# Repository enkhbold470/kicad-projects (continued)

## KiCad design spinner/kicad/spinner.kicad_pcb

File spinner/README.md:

# Spinner

A 12-24 V field-oriented-control BLDC motor controller: STM32G431, three IR2104 half bridges, MT6701 encoder, CAN FD.

| Layers | Size | Parts | Nets | Connections routed | Vias | ERC errors | DRC errors / unconnected / parity |
|---|---|---|---|---|---|---|---|
| 4 | 84 x 66 mm | 87 | 52 | 205 -> 0 open | 167 | 0 | 0 / 0 / 0 |

**Not fabricated, assembled or powered.** Every number on this page is measured by KiCad 10 on the files in this folder; the full measurements are in [`report.json`](report.json).

| | |
|---|---|
| KiCad project | [`kicad/`](kicad/) |
| Gerbers, BOM, CPL, STEP, schematic PDF | [`fab/`](fab/) |
| Renders | [top](media/top.png), [bottom](media/bottom.png) |
| Design process, every step as KiCad rendered it | [`media/design-process.mp4`](media/design-process.mp4) |

Spinner is a field-oriented-control (FOC) controller for a three-phase BLDC motor on a 12-24 V
bus. An STM32G431 drives three IR2104 half bridges and six 60 V MOSFETs, reads low-side shunts
through its own PGAs, and has an MT6701 magnetic encoder and CAN FD on the board. It was designed
with the HeyPCB method on KiCad 10 (the headless heypcb-kicad pipeline, routed by Freerouting
2.4.1) from the brief in `board.json`.

**It has not been fabricated, assembled or powered.** It carries no firmware. FOC firmware, such
as SimpleFOC or ST's MCSDK, is a separate project, and so are the timer, PGA and ADC settings that
the sense path below needs. Every gate number below is read from `report.json`. What this README
says about specific nets, pours, pads and silkscreen was read from `kicad/spinner.kicad_pcb` with
KiCad 10.0.6's pcbnew.

- **MCU:** STM32G431KBT6 (LQFP-32, Cortex-M4F, 170 MHz), with an 8 MHz crystal on the HSE and SWD on a 1.27 mm 2x5 Cortex debug header.
- **Inverter:** three IR2104 half-bridge drivers and six BSC028N06LS3 MOSFETs (60 V, 2.8 mOhm, PG-TDSON-8). Each phase takes one PWM input. One shared active-low enable, pulled down, keeps the bridge off while the MCU is in reset.
- **Current sense:** a 10 mOhm 2512 low-side shunt per phase. A 1k / 33k network biases each one onto about 97 mV, for the STM32G431's internal PGAs (OPAMP1/2/3 on PA1/PA7/PB0).
- **Encoder:** an MT6701CT magnetic angle sensor on the board, read over SSI on SPI1. Its MODE pin goes to a GPIO.
- **CAN:** CAN FD through a TCAN332G (3.3 V, 5 Mbps), on two 3-pin JST-GH ports for daisy-chaining. A slide switch puts a 120 R terminator across CANH and CANL.
- **Power:** 12-24 V in on a 5 mm screw terminal, with an SMAJ24A TVS and 2 x 220 uF / 35 V bulk capacitors.
  - A ferrite separates the regulators' input (VM_F) from the motor bus.
  - An AP63203 buck makes 3.3 V.
  - A 78L12 makes the 12 V gate-drive rail.
- **Sensing:** bus voltage through a 100k / 4.7k divider on PA0, and a 10k NTC near the W low side on PA3.
- **Other:** power, status and CAN LEDs; the motor on a 3-way 5 mm screw terminal; four M3 mounting holes.
- **Board:** 84 x 66 mm with 2 mm corners, 4 layers (F.Cu, In1 GND plane, In2 routing + VM pour, B.Cu), 1.6 mm thick in the gerber job.

## Substitutions from the request

| Asked for | On the board | Why |
|---|---|---|
| DRV8316 (integrated FETs and current sense) | 3 x IR2104 + 6 x BSC028N06LS3, plus three 10 mOhm low-side shunts read by the MCU's PGAs | KiCad 10 has no DRV8316 symbol. The integrated three-phase stages it does have are not workable here. The DRV8311 is rated for a 3-20 V supply. The MP6536DU operates at 26 V (28 V absolute maximum, MPS datasheet). Both are 0.4 mm-pitch QFNs whose single 0.2 mm pins cannot take a current-rated track: this pipeline runs Freerouting without neck-down, so a net's class width has to fit every pad on that net. Discrete MOSFETs carry the 1.5 mm motor class on F.Cu end to end. |
| TCAN1044 | TCAN332G (TCAN332GDR) | KiCad 10 has no TCAN1044 symbol. The TCAN332G is in Interface_CAN_LIN, runs CAN FD up to 5 Mbps, and runs from 3.3 V, so the board needs no 5 V rail. |
| STM32G431, LQFP-48 or LQFP-32 | STM32G431KBT6, LQFP-32 | Its 0.8 mm pitch is easier to route. Each function below was read from the symbol's own pin alternates. With the HSE crystal on PF0/PF1, TIM1's three complementary outputs do not all fit this package, so the inverter uses one PWM per phase and the IR2104's internal dead time. |

The MCU pins used (pin names read back from the run's netlist):

| Pin | Net | Function |
|---|---|---|
| PA8 / PA9 / PA10 | PWM_U / PWM_V / PWM_W | TIM1_CH1 / CH2 / CH3 |
| PB5 | DRV_EN | IR2104 ~SD (all three), 100k pull-down. PA15 and PB4 come out of reset with JTAG pull-ups, so neither is used here |
| PA1 / PA7 / PB0 | ISENSE_U / V / W | OPAMP1_VINP / OPAMP2_VINP / OPAMP3_VINP |
| PA0 | VM_SENSE | ADC1_IN1 |
| PA3 | TEMP | ADC1_IN4 |
| PA4 / PA5 / PA6 | ENC_CS / ENC_CLK / ENC_DO | SPI1_NSS / SCK / MISO to the MT6701 (Z/CSN, B/CLK, A/DO) |
| PB4 | ENC_MODE | MT6701 MODE (its 200k pull-up holds it high in reset) |
| PA11 / PA12 | CAN_RX / CAN_TX | FDCAN1 |
| PA13 / PA14 / PB3 / NRST | SWD | SWDIO / SWCLK / SWO / reset |
| PA15 / PB6 | LED_STAT / LED_CAN | red / orange LEDs (the green PWR LED is on 3V3) |
| PB8 | BOOT0 | 4.7k pull-down: boots from flash |

## Measured gates (run of 2026-10-01, from `report.json`)

| Gate | Result |
|---|---|
| Composition | 16 block instances → 87 parts, 52 nets, 10 no-connects |
| Part binding (`lcsc_pinned.json`) | 83 of 87 parts bound to an LCSC number, 0 unsourced, 0 identity conflicts. The four mounting holes (H1-H4) are not in the BOM: there is nothing to buy. 20 distinct Extended parts, about $60 in JLC loading fees |
| ERC (`kicad-cli sch erc --severity-all`) | 0 errors, 0 warnings |
| Netlist round trip | identical, 52 nets |
| Freerouting, rung 1, fanout on (kept) | 205 → **0 open** in 12.4 s, DRC score 0, 78 vias |
| Freerouting, rung 1, fanout off (measured for comparison) | 205 → 0 open in 10.8 s, DRC score 0, 80 vias. On a tie the first solve is kept. Neither solve needed the last-mile router |
| Copper | 734 tracks, 78 routing vias, 2215.3 mm of track (F.Cu 1357.9, In2 754.5, B.Cu 102.8). No class was narrowed: VMBUS and MOTOR stayed at 1.5 mm. After the import, 29 segments were widened to their class width; one 2.54 mm GND segment at the SWD header stays at the 0.15 mm board minimum, because 0.2 mm would not clear |
| Pours (only after a measured 0 open) | GND on F.Cu, In1 and B.Cu; **VM on In2** (`board.pours`); 89 stitching vias (167 vias in all); 0 open after the pour, after stitching and at the end |
| Silkscreen | 10 words, 6 pin labels and the 4 title lines placed; 0 stitching vias displaced; 66 designators re-seated and 12 hidden where nothing fit. The brief's front 12-24V word and J1's + / - marks did not land (see *Check these before ordering*) |
| DRC (`--severity-all --schematic-parity`, KiCad 10.0.6) | fresh, **0 errors, 0 unconnected, 0 parity**, 3 warnings |
| DFM (`jlcpcb_4layer`) | 0 errors, 1 warning (274 stock-footprint silk strokes at 0.12 mm; the fab prints them at its 0.15 mm minimum) |
| Fab gate | **ready**, no blockers; the JLC CPL corrected 9 rotations |

- **The 3 DRC warnings** are all `lib_footprint_mismatch`, on J1, J3 and SW1. The pipeline clipped their footprint silk where it ran past the board edge (11 strokes: 3 on J1, 3 on J3, 5 on SW1). J1 and J3 also carry the generated 3D body below in place of the library's model path.
- **3D bodies on the screw terminals are simplified.** The MaiXu MX126 footprints name a STEP file that the KiCad 10.0.6 install does not have. So J1 and J3 carry generated bodies (`kicad/models/maixu_mx126_5.0_02p.wrl` and `_03p.wrl`): a block over the footprint's fab outline, 10 mm tall, with a screw head over each pin and a wire opening beside it. They are envelopes read off the footprint, not vendor models. They show in the renders, but `fab/spinner.step` has no body for J1 or J3.

## Silkscreen

- **Front:** SWD at the debug header; PWR, STAT and CAN at the three LEDs; ENC at the encoder; MOTOR at the motor terminal; CAN above each GH port (J4's above J4, J5's between the two ports).
- **Terminator switch (SW1):** 120R beside pin 1, the throw that joins the 120 R's free end (U8_TERM, on the common pin) to CANL (U8_CANL); OFF beside pin 3, which is not connected.
- **Motor terminal (J3):** U, V and W beside the pins on the back; on the front only U, because J3's own footprint silk blocks the V and W spots.
- **Supply terminal (J1):** +12-24V beside pin 1 and - beside pin 2, on the back only. See *Check these before ordering*.
- **Back:** the four title lines "Spinner", "FOC BLDC / STM32G431 / CAN FD", "rev A heypcb-kicad" and "12-24 V, not fabricated".

## Check these before ordering

The board passes ERC, the netlist round trip, routing, DRC (errors, unconnected and parity), DFM and the fab gate in KiCad. It has not been fabricated, assembled or powered.

**Current**
- **Track rating.** The VMBUS class (VM) and the MOTOR class (PHASE_U/V/W, LSS_U/V/W) are 1.5 mm wide and declared at `currentA` 3. By the IPC-2221 formula in heypcb-kicad's `route.py` (`ipc2221_amps`), at a 10 C rise, 1.5 mm carries:
  - about 3.2 A on 1 oz outer copper;
  - about 1.0 A on 0.5 oz inner copper (1.6 A at 1 oz inner).
- **Inner copper weight.** The gerber job lists 35 um copper on all four layers. That is KiCad's default stackup, not a fab's. The inner-copper figures here give both 0.5 oz and 1 oz; choose the inner weight when ordering.
- **Vias.** A VMBUS via is 1.2 / 0.7 mm. It carries about 3.4 A at a 10 C rise: the same formula with the outer-layer constant, applied to a barrel of 25 um plating around the 0.7 mm drill. The VMBUS note in `board.json` records why a larger via was not used.
- **Where the copper ran.** This was read from `kicad/spinner.kicad_pcb` with pcbnew, not from report.json. Positions are in mm from the board's top-left corner.
  - All three phases (U 61.2, V 55.9, W 55.3 mm) and all three shunt links (9.8 mm each) are 1.5 mm on F.Cu, with no vias. That copper is 1 oz outer copper end to end.
  - **VM changes layer.** It is 90.8 mm of 1.5 mm track: 75.1 mm on F.Cu and 15.7 mm on In2, between 2 VMBUS vias (1.2 / 0.7 mm). One via is next to C1, at (35.6, 29.8); the other is beside C20, at (40.8, 16.3).
  - Phases V and W, the bulk capacitors, the TVS, the ferrite and J1 are joined on F.Cu. Phase U's high side (Q1's drain, C19, C20) reaches the rest of VM only through In2 and the via beside C20. That one via carries all of phase U's high-side current: about 3.4 A of rating against the 3 A class.
  - The In2 stretch lies wholly inside the In2 VM pour; it is not a lone inner track. Measured square to the track every 0.1 mm, more than 1 mm from either via, the poured copper around it is at least 13.0 mm wide; at the via beside C20 it is 5.1 mm. The narrowest cut through the In2 VM copper between the two vias is at least 8.6 mm (a max-flow on a 0.1 mm raster, which can only undercount). Treated as a track, 8.6 mm is about 3.4 A at 0.5 oz inner (5.7 A at 1 oz) by the same formula. A lone 1.5 mm inner track would carry the 1.0 A above.
  - The In2 VM pour is 4417 mm² after fill, in one island. It joins VM at J1 pin 1 (thermal spokes; this is the only through-hole VM pad), at both VM vias and along all of VM's In2 track.
- **Silicon and connectors.**
  - MOSFETs: 100 A in the KiCad symbol's description.
  - Terminals: 10 A per contact, from the MX126 catalogue rows.
  - JST-GH: 1 A per contact (catalogue row).
  - Shunts: 10 mOhm, 3 W.
  - None of these is the limit; the copper is.
- **Current-sense range.** At PGA gain 16 the bias sits near 1.55 V, which gives roughly +-10 A full scale. The gain and offset are firmware choices. Low-side shunts read phase current only while each low-side MOSFET conducts, so sample in the PWM centre.

**Thermal**
- **MOSFETs.** There are no thermal vias under the drain pads, because the stock TDSON-8-1 footprint has none, and no heatsink. These are estimates from datasheet and catalogue values, not measurements:
  - conduction loss is small (2.8 mOhm at 3 A is about 25 mW per FET);
  - switching loss dominates. The IR2104 drives 130 mA / 270 mA (catalogue row) into about 31 nC of gate charge, so the edges take a few hundred ns: roughly 0.25 W per hard-switched FET at 24 V, 3 A and 20 kHz.
  - Watch TH1, the NTC near the W low side.
- **Regulators.**
  - The 78L12 drops (VM - 12 V) at a few mA of gate current: about 50 mW at 24 V.
  - The AP63203's load is the logic: on the order of 100 mA (an estimate, not measured) against its 2 A rating.

**Voltage**
- **Upper limit: 24 V nominal; a 6S pack at 25.2 V is fine.**
  - The TVS breaks down between 26.7 and 29.5 V and clamps at 38.9 V at 10.3 A (SMAJ24A catalogue rows).
  - The electrolytics, the AP63203 (absolute maximum) and the 78L12 (catalogue row) are all 35 V parts.
  - The bootstrap diodes are 40 V and the MOSFETs 60 V.
  - **Regenerative braking can pump the bus up**: limit regen in firmware or add a brake resistor.
- **Lower limit: 12 V.** The 78L12 drops out (1.7 V) to about 10.3 V there. That is the bottom of the IR2104's 10-20 V supply range; below a 12 V bus the gate drive is out of specification.
- **No reverse-polarity protection and no fuse.** A reversed supply forward-biases the TVS. Fuse the supply lead.
- **J1's polarity is printed on the back only.** The back reads +12-24V beside pin 1 (VM) and - beside pin 2 (GND). The - sits between the two pins, nearer pin 2. On the front, pin 1 is marked only by the footprint's pin-1 triangle, for three reasons:
  - The brief's + / - marks (`silk.polarity`) do not land: every spot the silk stage tries is 1.9-2.3 mm from the pad centre and overlaps J1's 2.8 mm pads.
  - The front pin labels hit J1's own footprint silk.
  - The brief's front 12-24V word (`silk.words`) finds no free spot: L1, D1, J1's pin-1 mark, a routed VM_F via and the board edge surround the terminal.

  Reserving that spot with a via keep-out was tried. The reroute it caused put phase U's sense line (ISENSE_U) on In2 beside VM's stretch and cut the In2 copper between the two VM vias to about 2.5 mm, so the brief does not do it. Mark the supply lead.
- **IR2104 logic threshold.** VIH is 3.0 V minimum, and the MCU drives 3.3 V: a 0.3 V margin.

**Mechanics and sourcing**
- **Encoder.** The MT6701 sits in the lower-left logic area, marked ENC. The motor's diametric magnet (6 mm x 2.5 mm recommended) has to sit 0.5-2.0 mm above the package centre, within 0.3 mm (MagnTek datasheet). Plan the motor mount around it.
- **CAN.** The GH pin order (1 CANH, 2 CANL, 3 GND) is this board's own choice. Check it against your cables. SW1's words name its throws: 120R beside pin 1, the throw that terminates the bus, and OFF beside pin 3. Which slider position closes which throw was not checked against the PCM12 datasheet.
- **Part numbers.** All 36 part numbers in `fab/spinner_bom.csv` come from heypcb-kicad's pinned catalogue table: 23 rows dated 2026-09-30 (22 of them marked as live lookups) and 13 dated 2026-06-23 to 2026-07-03. Stock and Basic/Extended class go stale; re-check before ordering. The TCAN332GDR (stock 253) and the SM03B-GHS-TB (stock 494) had the lowest stock of those rows.

## Files

- `board.json`: the brief the pipeline built everything here from.
- `report.json`: the run's gate report, the source of every gate number above.
- `kicad/`: `spinner.kicad_pro`, `spinner.kicad_sch`, `spinner.kicad_pcb` (routed and poured) and `models/` (the two generated terminal bodies).
- `fab/spinner_gerbers.zip`: 11 layer gerbers, the gerber job, the drill file and the drill map.
- `fab/spinner_bom.csv` (36 part rows, 83 parts), `fab/spinner_cpl_jlc.csv` (JLC placement for the 81 SMD parts, rotations corrected; the through-hole J1 and J3 are not in it), `fab/spinner_pos.csv` (KiCad placement), `fab/spinner_schematic.pdf`, `fab/spinner.step`.
- `media/`: `hero.png`, `top.png`, `bottom.png` and the design-process video (`design-process.mp4`, `design-process.gif`).

## Reproduce

From the heypcb-kicad repository:

```bash
./run.sh --board boards/spinner              # every stage, with the 3D renders and the video
./run.sh --board boards/spinner --no-media   # stop before the 3D frames, renders and video
```

Placement walks parts in reference order, and the Specctra file is written in an order set by
content alone. So the brief is meant to place and route the same way every time. The final brief
was built three times on 2026-10-01: once from the board stage and twice in full, the last with
media. All three routed 205 → 0 open with the same copper (734 tracks, 78 vias, 2215.3 mm) and
placed the same silkscreen. The two full runs gave the same copper and silkscreen measurements
here; only the solve times differed, by 0.1 s.

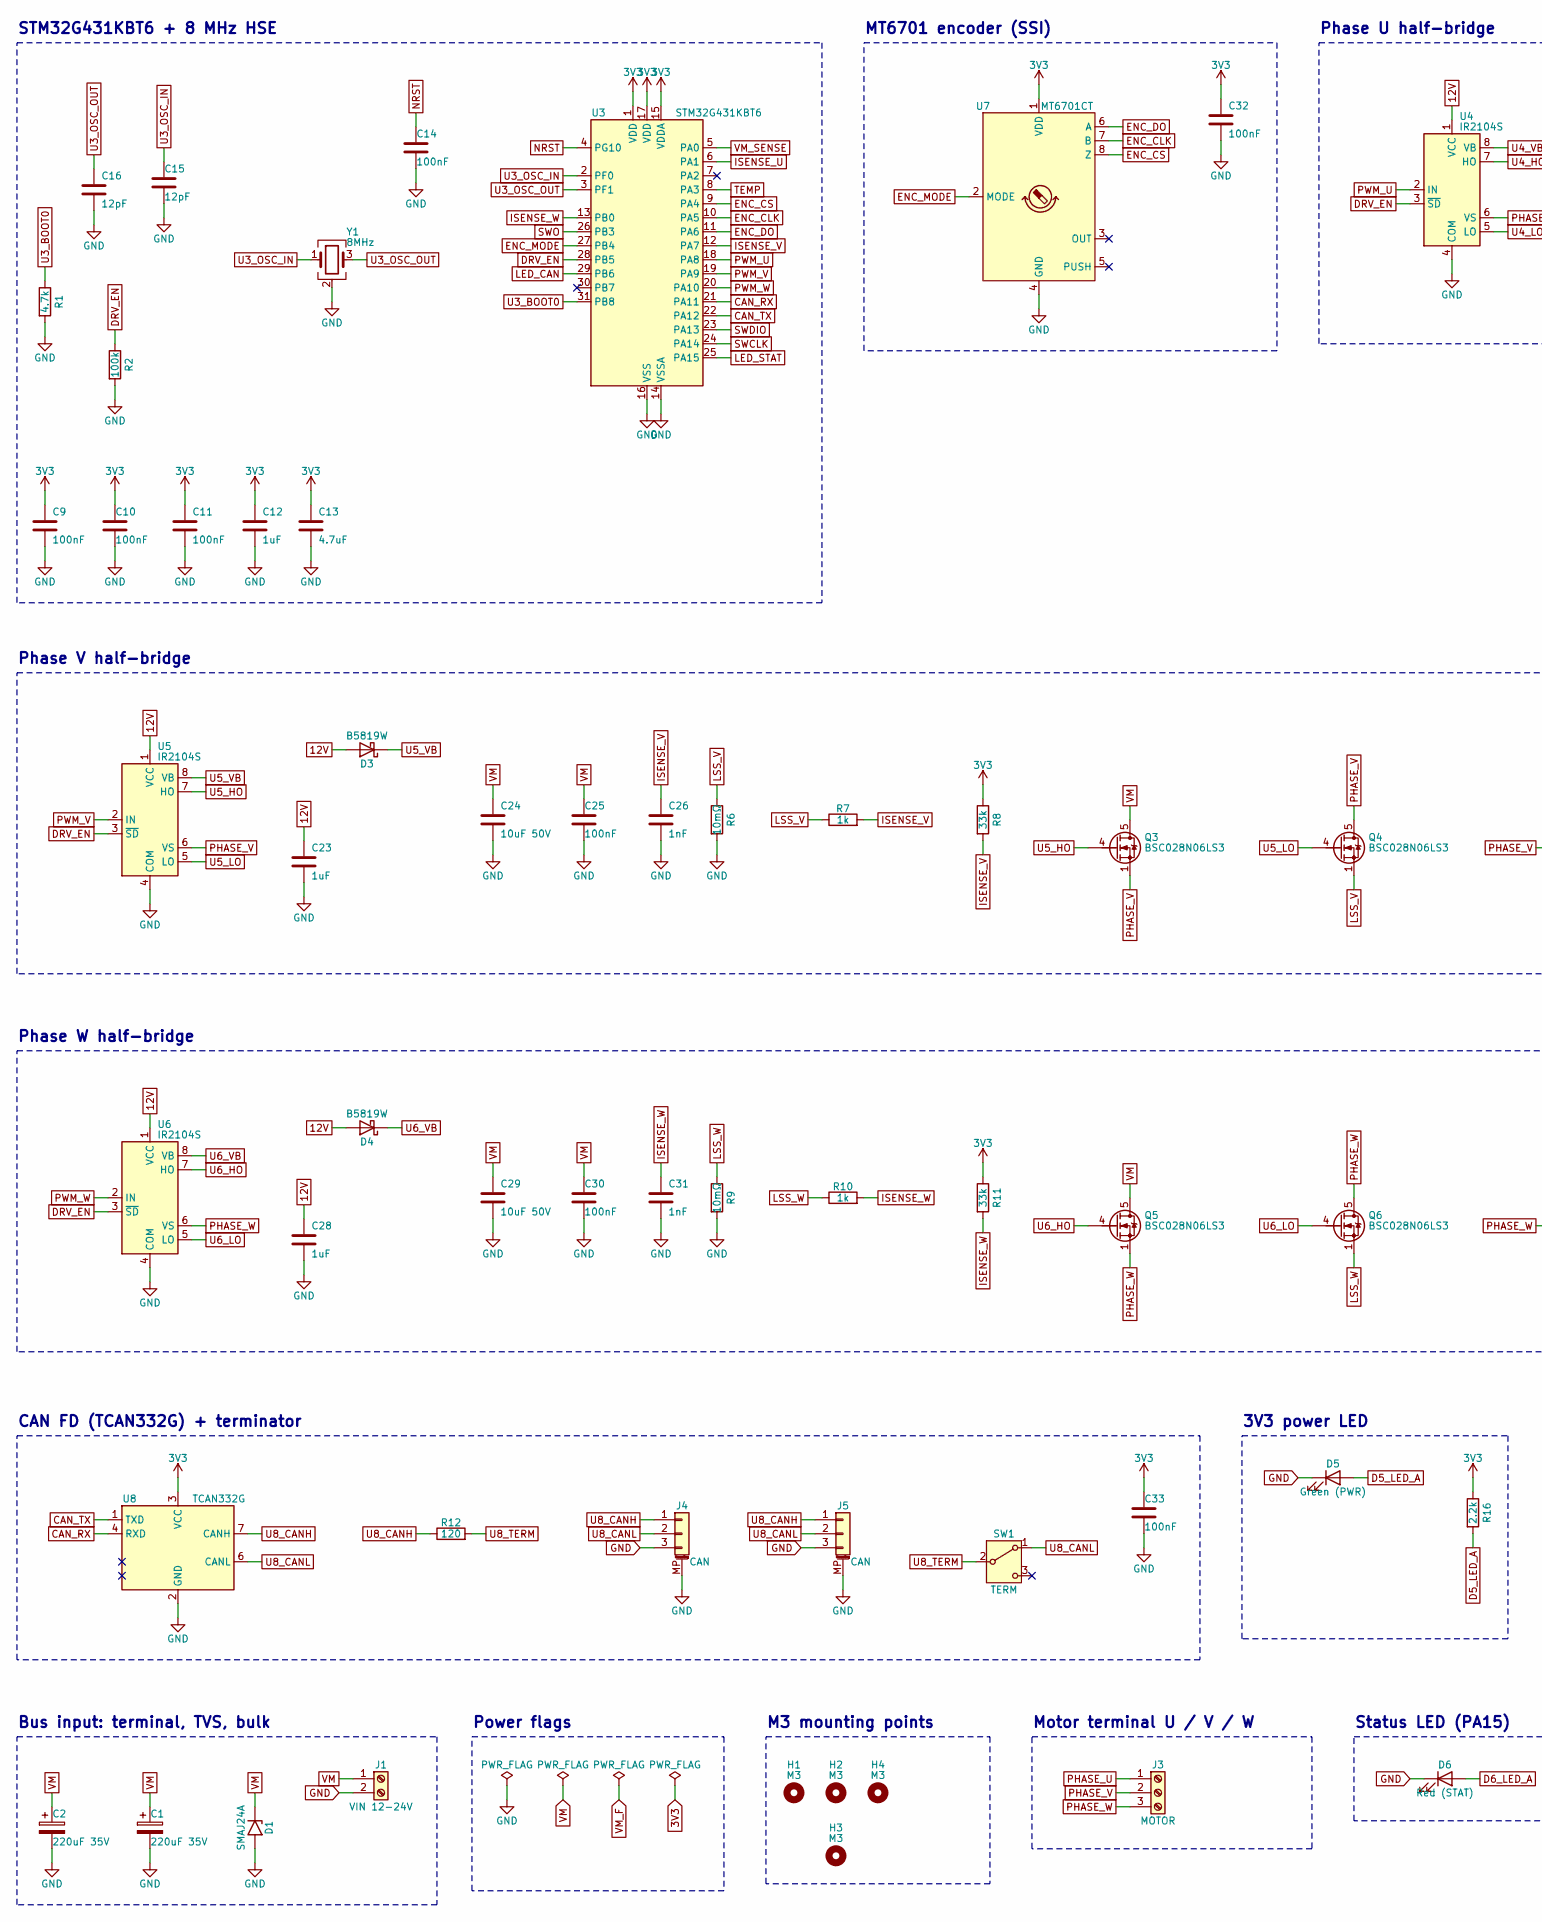
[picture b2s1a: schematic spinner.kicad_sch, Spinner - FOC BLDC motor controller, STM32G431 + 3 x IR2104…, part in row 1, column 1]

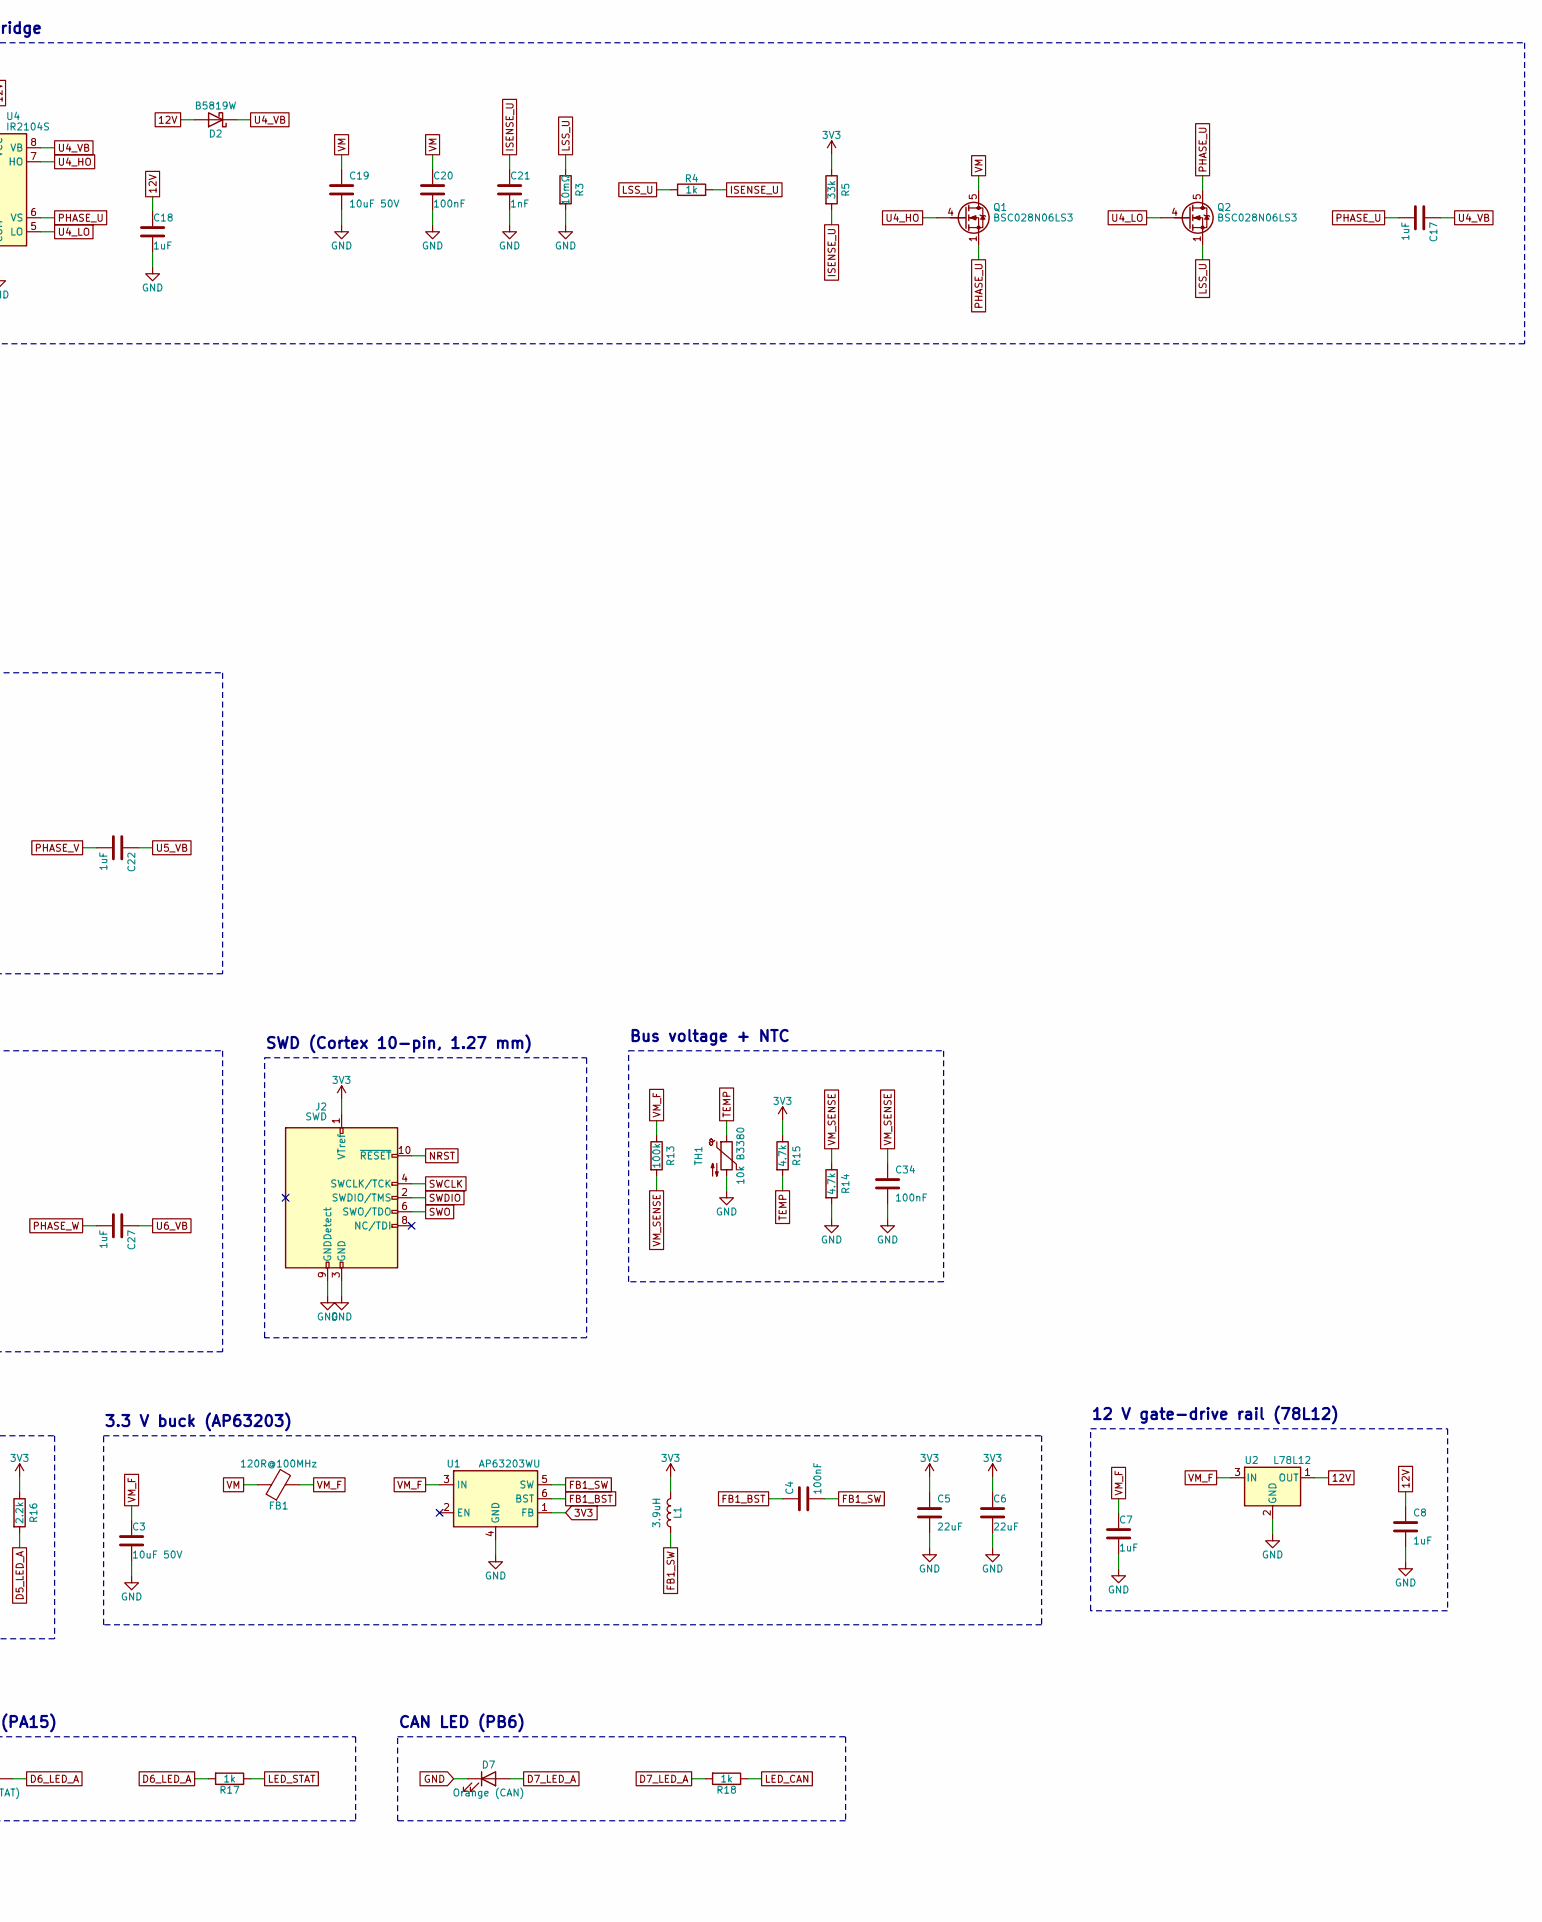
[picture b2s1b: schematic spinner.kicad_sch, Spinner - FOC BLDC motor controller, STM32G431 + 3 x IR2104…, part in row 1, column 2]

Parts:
C1, C2: 220uF 35V; CP_Elec_8x10.5; MPN UCD1V221MNL1GS; LCSC C136294
C3, C19, C24, C29: 10uF 50V; C_0805_2012Metric; MPN GRM21BR61H106KE43L; LCSC C440198
C4, C9, C10, C11, C14, C20, C25, C30, C32, C33, C34: 100nF; C_0603_1608Metric; MPN CC0603KRX7R9BB104; LCSC C14663
C5, C6: 22uF; C_0805_2012Metric; MPN CL21A226MAQNNNE; LCSC C45783
C7, C8, C12, C17, C18, C22, C23, C27, C28: 1uF; C_0603_1608Metric; MPN CL10A105KB8NNNC; LCSC C15849
C13: 4.7uF; C_0805_2012Metric; MPN CL21A475KAQNNNE; LCSC C1779
C15, C16: 12pF; C_0603_1608Metric; MPN CL10C120JB8NNNC; LCSC C38523
C21, C26, C31: 1nF; C_0603_1608Metric; MPN CL10B102KB8NNNC; LCSC C1588
D1: SMAJ24A; D_SMA; MPN SMAJ24A; LCSC C19077541
D2, D3, D4: B5819W; D_SOD-123; MPN B5819W SL; LCSC C8598
D5: Green (PWR); LED_0603_1608Metric; MPN KT-0603G; LCSC C12624
D6: Red (STAT); LED_0603_1608Metric; MPN KT-0603R; LCSC C2286
D7: Orange (CAN); LED_0603_1608Metric; MPN XL-1608UOC-06; LCSC C965800
FB1: 120R@100MHz; L_0603_1608Metric; MPN BLM18PG121SN1D; LCSC C14709
H1, H2, H3, H4: M3; MountingHole_3.2mm_M3
J1: VIN 12-24V; TerminalBlock_MaiXu_MX126-5.0-02P_1x02_P5.00mm; MPN MX126-5.0-02P-GN01-Cu-S-A; LCSC C5188434
J2: SWD; PinHeader_2x05_P1.27mm_Vertical_SMD; MPN PZ127VS-12-10-H10-A38; LCSC C2935458
J3: MOTOR; TerminalBlock_MaiXu_MX126-5.0-03P_1x03_P5.00mm; MPN MX126-5.0-03P-GN01-Cu-S-A; LCSC C5188435
J4, J5: CAN; JST_GH_SM03B-GHS-TB_1x03-1MP_P1.25mm_Horizontal; MPN SM03B-GHS-TB(LF)(SN); LCSC C514175
L1: 3.9uH; L_Changjiang_FNR4030S; MPN FNR4030S3R9MT; LCSC C167872
Q1, Q2, Q3, Q4, Q5, Q6: BSC028N06LS3; TDSON-8-1; MPN BSC028N06LS3 G; LCSC C534316
R1, R14, R15: 4.7k; R_0603_1608Metric; MPN 0603WAF4701T5E; LCSC C23162
R2, R13: 100k; R_0603_1608Metric; MPN 0603WAF1003T5E; LCSC C25803
R3, R6, R9: 10mΩ; R_2512_6332Metric; MPN PA2512FKE7T0R01E; LCSC C375691
R4, R7, R10, R17, R18: 1k; R_0603_1608Metric; MPN 0603WAF1001T5E; LCSC C21190
R5, R8, R11: 33k; R_0603_1608Metric; MPN 0603WAF3302T5E; LCSC C4216
R12: 120; R_0603_1608Metric; MPN 0603WAF1200T5E; LCSC C22787
R16: 2.2k; R_0603_1608Metric; MPN 0603WAF2201T5E; LCSC C4190
SW1: TERM; SW_SPDT_PCM12; MPN PCM12SMTR; LCSC C221841
TH1: 10k B3380; R_0603_1608Metric; MPN NCP18XH103F03RB; LCSC C13564
U1: AP63203WU; TSOT-23-6; MPN AP63203WU-7; LCSC C780769
U2: L78L12; SOT-89-3; MPN L78L12ABUTR; LCSC C915681
U3: STM32G431KBT6; LQFP-32_7x7mm_P0.8mm; MPN STM32G431KBT6; LCSC C529357
U4, U5, U6: IR2104S; SOIC-8_3.9x4.9mm_P1.27mm; MPN IR2104STRPBF; LCSC C2960
U7: MT6701CT; SO-8_3.9x4.9mm_P1.27mm; MPN MT6701CT-STD; LCSC C2856764
U8: TCAN332G; SOIC-8_3.9x4.9mm_P1.27mm; MPN TCAN332GDR; LCSC C191010
Y1: 8MHz; Crystal_SMD_3225-4Pin_3.2x2.5mm; MPN TAXM8M4RDBCCT2T; LCSC C400090

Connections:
3V3: C5.1, C6.1, C9.1, C10.1, C11.1, C12.1, C13.1, C32.1, C33.1, J2.1 (VTref), L1.2, R5.1, R8.1, R11.1, R15.1, R16.1, U1.1 (FB), U3.1 (VDD), U3.15 (VDDA), U3.17 (VDD), U7.1 (VDD), U8.3 (VCC)
12V: C8.1, C18.1, C23.1, C28.1, D2.2 (A), D3.2 (A), D4.2 (A), U2.1 (OUT), U4.1 (VCC), U5.1 (VCC), U6.1 (VCC)
CAN_RX: U3.21 (PA11), U8.4 (RXD)
CAN_TX: U3.22 (PA12), U8.1 (TXD)
D5_LED_A: D5.2 (A), R16.2
D6_LED_A: D6.2 (A), R17.2
D7_LED_A: D7.2 (A), R18.2
DRV_EN: R2.1, U3.28 (PB5), U4.3 (~SD), U5.3 (~SD), U6.3 (~SD)
ENC_CLK: U3.10 (PA5), U7.7 (B)
ENC_CS: U3.9 (PA4), U7.8 (Z)
ENC_DO: U3.11 (PA6), U7.6 (A)
ENC_MODE: U3.27 (PB4), U7.2 (MODE)
FB1_BST: C4.1, U1.6 (BST)
FB1_SW: C4.2, L1.1, U1.5 (SW)
GND: C1.2, C2.2, C3.2, C5.2, C6.2, C7.2, C8.2, C9.2, C10.2, C11.2, C12.2, C13.2, C14.2, C15.2, C16.2, C18.2, C19.2, C20.2, C21.2, C23.2, C24.2, C25.2, C26.2, C28.2, C29.2, C30.2, C31.2, C32.2, C33.2, C34.2, D1.2 (A2), D5.1 (K), D6.1 (K), D7.1 (K), J1.2, J2.3 (GND), J2.5 (GND), J2.9 (GNDDetect), J4.3, J4.MP (MountPin), J5.3, J5.MP (MountPin), R1.2, R2.2, R3.2, R6.2, R9.2, R14.2, TH1.2, U1.4 (GND), U2.2 (GND), U3.14 (VSSA), U3.16 (VSS), U3.32 (VSS), U4.4 (COM), U5.4 (COM), U6.4 (COM), U7.4 (GND), U8.2 (GND), Y1.2 (G), Y1.4 (G)
ISENSE_U: C21.1, R4.2, R5.2, U3.6 (PA1)
ISENSE_V: C26.1, R7.2, R8.2, U3.12 (PA7)
ISENSE_W: C31.1, R10.2, R11.2, U3.13 (PB0)
LED_CAN: R18.1, U3.29 (PB6)
LED_STAT: R17.1, U3.25 (PA15)
LSS_U: Q2.1 (S), Q2.2 (S), Q2.3 (S), R3.1, R4.1
LSS_V: Q4.1 (S), Q4.2 (S), Q4.3 (S), R6.1, R7.1
LSS_W: Q6.1 (S), Q6.2 (S), Q6.3 (S), R9.1, R10.1
NRST: C14.1, J2.10 (~RESET), U3.4 (PG10)
PHASE_U: C17.2, J3.1, Q1.1 (S), Q1.2 (S), Q1.3 (S), Q2.5 (D), U4.6 (VS)
PHASE_V: C22.2, J3.2, Q3.1 (S), Q3.2 (S), Q3.3 (S), Q4.5 (D), U5.6 (VS)
PHASE_W: C27.2, J3.3, Q5.1 (S), Q5.2 (S), Q5.3 (S), Q6.5 (D), U6.6 (VS)
PWM_U: U3.18 (PA8), U4.2 (IN)
PWM_V: U3.19 (PA9), U5.2 (IN)
PWM_W: U3.20 (PA10), U6.2 (IN)
SWCLK: J2.4 (SWCLK/TCK), U3.24 (PA14)
SWDIO: J2.2 (SWDIO/TMS), U3.23 (PA13)
SWO: J2.6 (SWO/TDO), U3.26 (PB3)
TEMP: R15.2, TH1.1, U3.8 (PA3)
U3_BOOT0: R1.1, U3.31 (PB8)
U3_OSC_IN: C15.1, U3.2 (PF0), Y1.1
U3_OSC_OUT: C16.1, U3.3 (PF1), Y1.3
U4_HO: Q1.4 (G), U4.7 (HO)
U4_LO: Q2.4 (G), U4.5 (LO)
U4_VB: C17.1, D2.1 (K), U4.8 (VB)
U5_HO: Q3.4 (G), U5.7 (HO)
U5_LO: Q4.4 (G), U5.5 (LO)
U5_VB: C22.1, D3.1 (K), U5.8 (VB)
U6_HO: Q5.4 (G), U6.7 (HO)
U6_LO: Q6.4 (G), U6.5 (LO)
U6_VB: C27.1, D4.1 (K), U6.8 (VB)
U8_CANH: J4.1, J5.1, R12.1, U8.7 (CANH)
U8_CANL: J4.2, J5.2, SW1.1 (A), U8.6 (CANL)
U8_TERM: R12.2, SW1.2 (B)
VM: C1.1, C2.1, C19.1, C20.1, C24.1, C25.1, C29.1, C30.1, D1.1 (A1), FB1.1, J1.1, Q1.5 (D), Q3.5 (D), Q5.5 (D)
VM_F: C3.1, C7.1, FB1.2, R13.1, U1.3 (IN), U2.3 (IN)
VM_SENSE: C34.1, R13.2, R14.1, U3.5 (PA0)

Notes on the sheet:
Bus input: terminal, TVS, bulk
3.3 V buck (AP63203)
12 V gate-drive rail (78L12)
STM32G431KBT6 + 8 MHz HSE
SWD (Cortex 10-pin, 1.27 mm)
Phase U half-bridge
Phase V half-bridge
Phase W half-bridge
Motor terminal U / V / W
MT6701 encoder (SSI)
CAN FD (TCAN332G) + terminator
Bus voltage + NTC
3V3 power LED
Status LED (PA15)
CAN LED (PB6)
M3 mounting points
Power flags

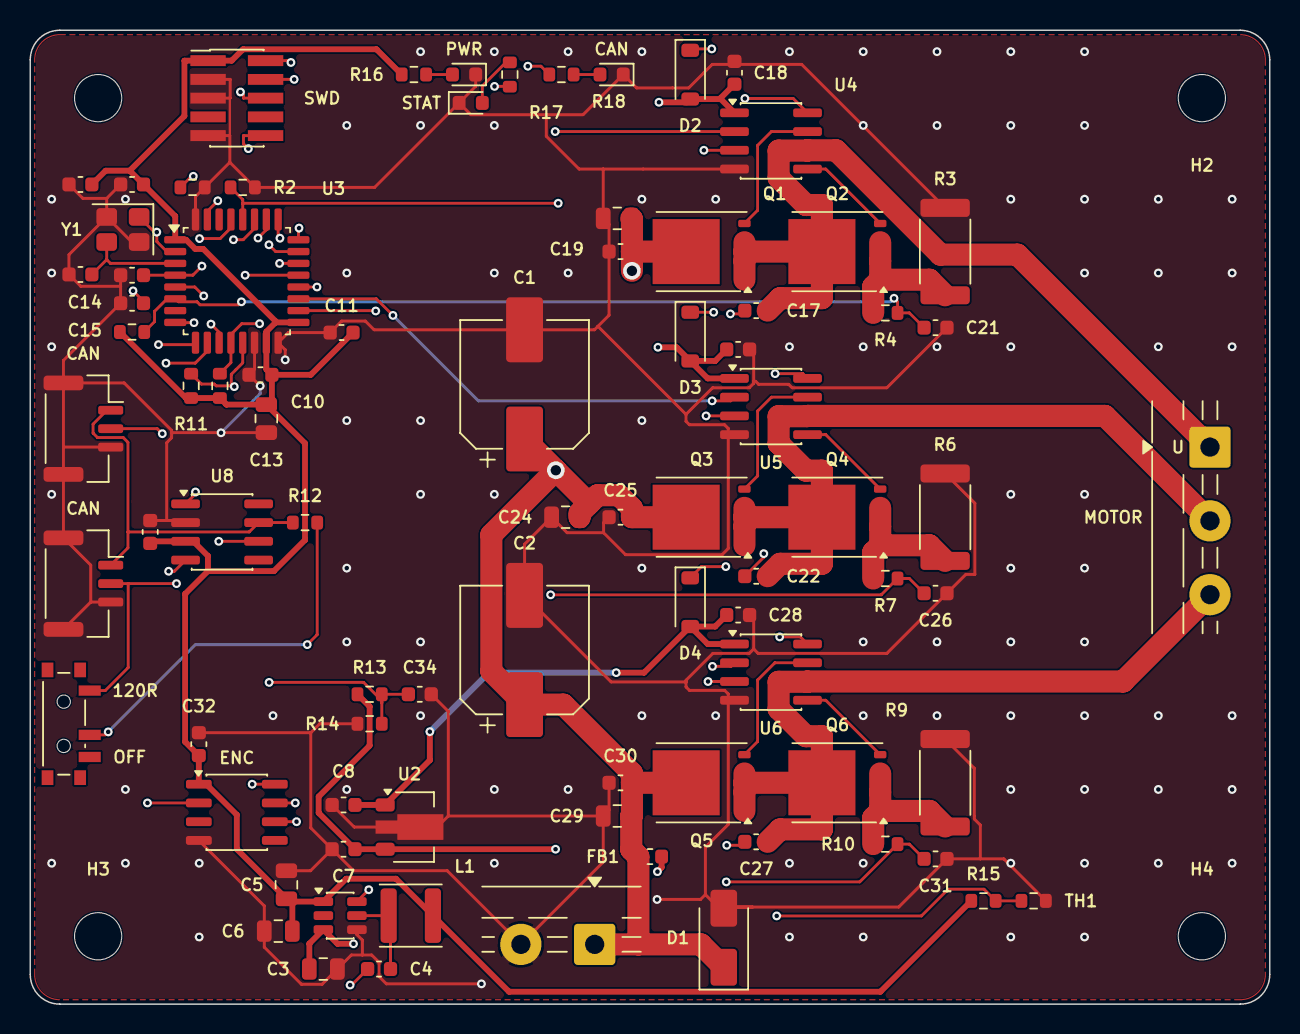
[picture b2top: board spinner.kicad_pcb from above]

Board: 4 copper layers, 84.0 x 66.0 mm, 87 parts (0 on the bottom side), 52 nets.

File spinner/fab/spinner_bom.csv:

"Reference","Value","Footprint","MPN","LCSC","Qty"
"C1,C2","220uF 35V","Capacitor_SMD:CP_Elec_8x10.5","UCD1V221MNL1GS","C136294","2"
"C3,C19,C24,C29","10uF 50V","Capacitor_SMD:C_0805_2012Metric","GRM21BR61H106KE43L","C440198","4"
"C4,C9,C10,C11,C14,C20,C25,C30,C32,C33,C34","100nF","Capacitor_SMD:C_0603_1608Metric","CC0603KRX7R9BB104","C14663","11"
"C5,C6","22uF","Capacitor_SMD:C_0805_2012Metric","CL21A226MAQNNNE","C45783","2"
"C7,C8,C12,C17,C18,C22,C23,C27,C28","1uF","Capacitor_SMD:C_0603_1608Metric","CL10A105KB8NNNC","C15849","9"
"C13","4.7uF","Capacitor_SMD:C_0805_2012Metric","CL21A475KAQNNNE","C1779","1"
"C15,C16","12pF","Capacitor_SMD:C_0603_1608Metric","CL10C120JB8NNNC","C38523","2"
"C21,C26,C31","1nF","Capacitor_SMD:C_0603_1608Metric","CL10B102KB8NNNC","C1588","3"
"D1","SMAJ24A","Diode_SMD:D_SMA","SMAJ24A","C19077541","1"
"D2,D3,D4","B5819W","Diode_SMD:D_SOD-123","B5819W SL","C8598","3"
"D5","Green (PWR)","LED_SMD:LED_0603_1608Metric","KT-0603G","C12624","1"
"D6","Red (STAT)","LED_SMD:LED_0603_1608Metric","KT-0603R","C2286","1"
"D7","Orange (CAN)","LED_SMD:LED_0603_1608Metric","XL-1608UOC-06","C965800","1"
"FB1","120R@100MHz","Inductor_SMD:L_0603_1608Metric","BLM18PG121SN1D","C14709","1"
"J1","VIN 12-24V","TerminalBlock:TerminalBlock_MaiXu_MX126-5.0-02P_1x02_P5.00mm","MX126-5.0-02P-GN01-Cu-S-A","C5188434","1"
"J2","SWD","Connector_PinHeader_1.27mm:PinHeader_2x05_P1.27mm_Vertical_SMD","PZ127VS-12-10-H10-A38","C2935458","1"
"J3","MOTOR","TerminalBlock:TerminalBlock_MaiXu_MX126-5.0-03P_1x03_P5.00mm","MX126-5.0-03P-GN01-Cu-S-A","C5188435","1"
"J4,J5","CAN","Connector_JST:JST_GH_SM03B-GHS-TB_1x03-1MP_P1.25mm_Horizontal","SM03B-GHS-TB(LF)(SN)","C514175","2"
"L1","3.9uH","Inductor_SMD:L_Changjiang_FNR4030S","FNR4030S3R9MT","C167872","1"
"Q1,Q2,Q3,Q4,Q5,Q6","BSC028N06LS3","Package_TO_SOT_SMD:TDSON-8-1","BSC028N06LS3 G","C534316","6"
"R1,R14,R15","4.7k","Resistor_SMD:R_0603_1608Metric","0603WAF4701T5E","C23162","3"
"R2,R13","100k","Resistor_SMD:R_0603_1608Metric","0603WAF1003T5E","C25803","2"
"R3,R6,R9","10mΩ","Resistor_SMD:R_2512_6332Metric","PA2512FKE7T0R01E","C375691","3"
"R4,R7,R10,R17,R18","1k","Resistor_SMD:R_0603_1608Metric","0603WAF1001T5E","C21190","5"
"R5,R8,R11","33k","Resistor_SMD:R_0603_1608Metric","0603WAF3302T5E","C4216","3"
"R12","120","Resistor_SMD:R_0603_1608Metric","0603WAF1200T5E","C22787","1"
"R16","2.2k","Resistor_SMD:R_0603_1608Metric","0603WAF2201T5E","C4190","1"
"SW1","TERM","Button_Switch_SMD:SW_SPDT_PCM12","PCM12SMTR","C221841","1"
"TH1","10k B3380","Resistor_SMD:R_0603_1608Metric","NCP18XH103F03RB","C13564","1"
"U1","AP63203WU","Package_TO_SOT_SMD:TSOT-23-6","AP63203WU-7","C780769","1"
"U2","L78L12","Package_TO_SOT_SMD:SOT-89-3","L78L12ABUTR","C915681","1"
"U3","STM32G431KBT6","Package_QFP:LQFP-32_7x7mm_P0.8mm","STM32G431KBT6","C529357","1"
"U4,U5,U6","IR2104S","Package_SO:SOIC-8_3.9x4.9mm_P1.27mm","IR2104STRPBF","C2960","3"
"U7","MT6701CT","Package_SO:SO-8_3.9x4.9mm_P1.27mm","MT6701CT-STD","C2856764","1"
"U8","TCAN332G","Package_SO:SOIC-8_3.9x4.9mm_P1.27mm","TCAN332GDR","C191010","1"
"Y1","8MHz","Crystal:Crystal_SMD_3225-4Pin_3.2x2.5mm","TAXM8M4RDBCCT2T","C400090","1"
